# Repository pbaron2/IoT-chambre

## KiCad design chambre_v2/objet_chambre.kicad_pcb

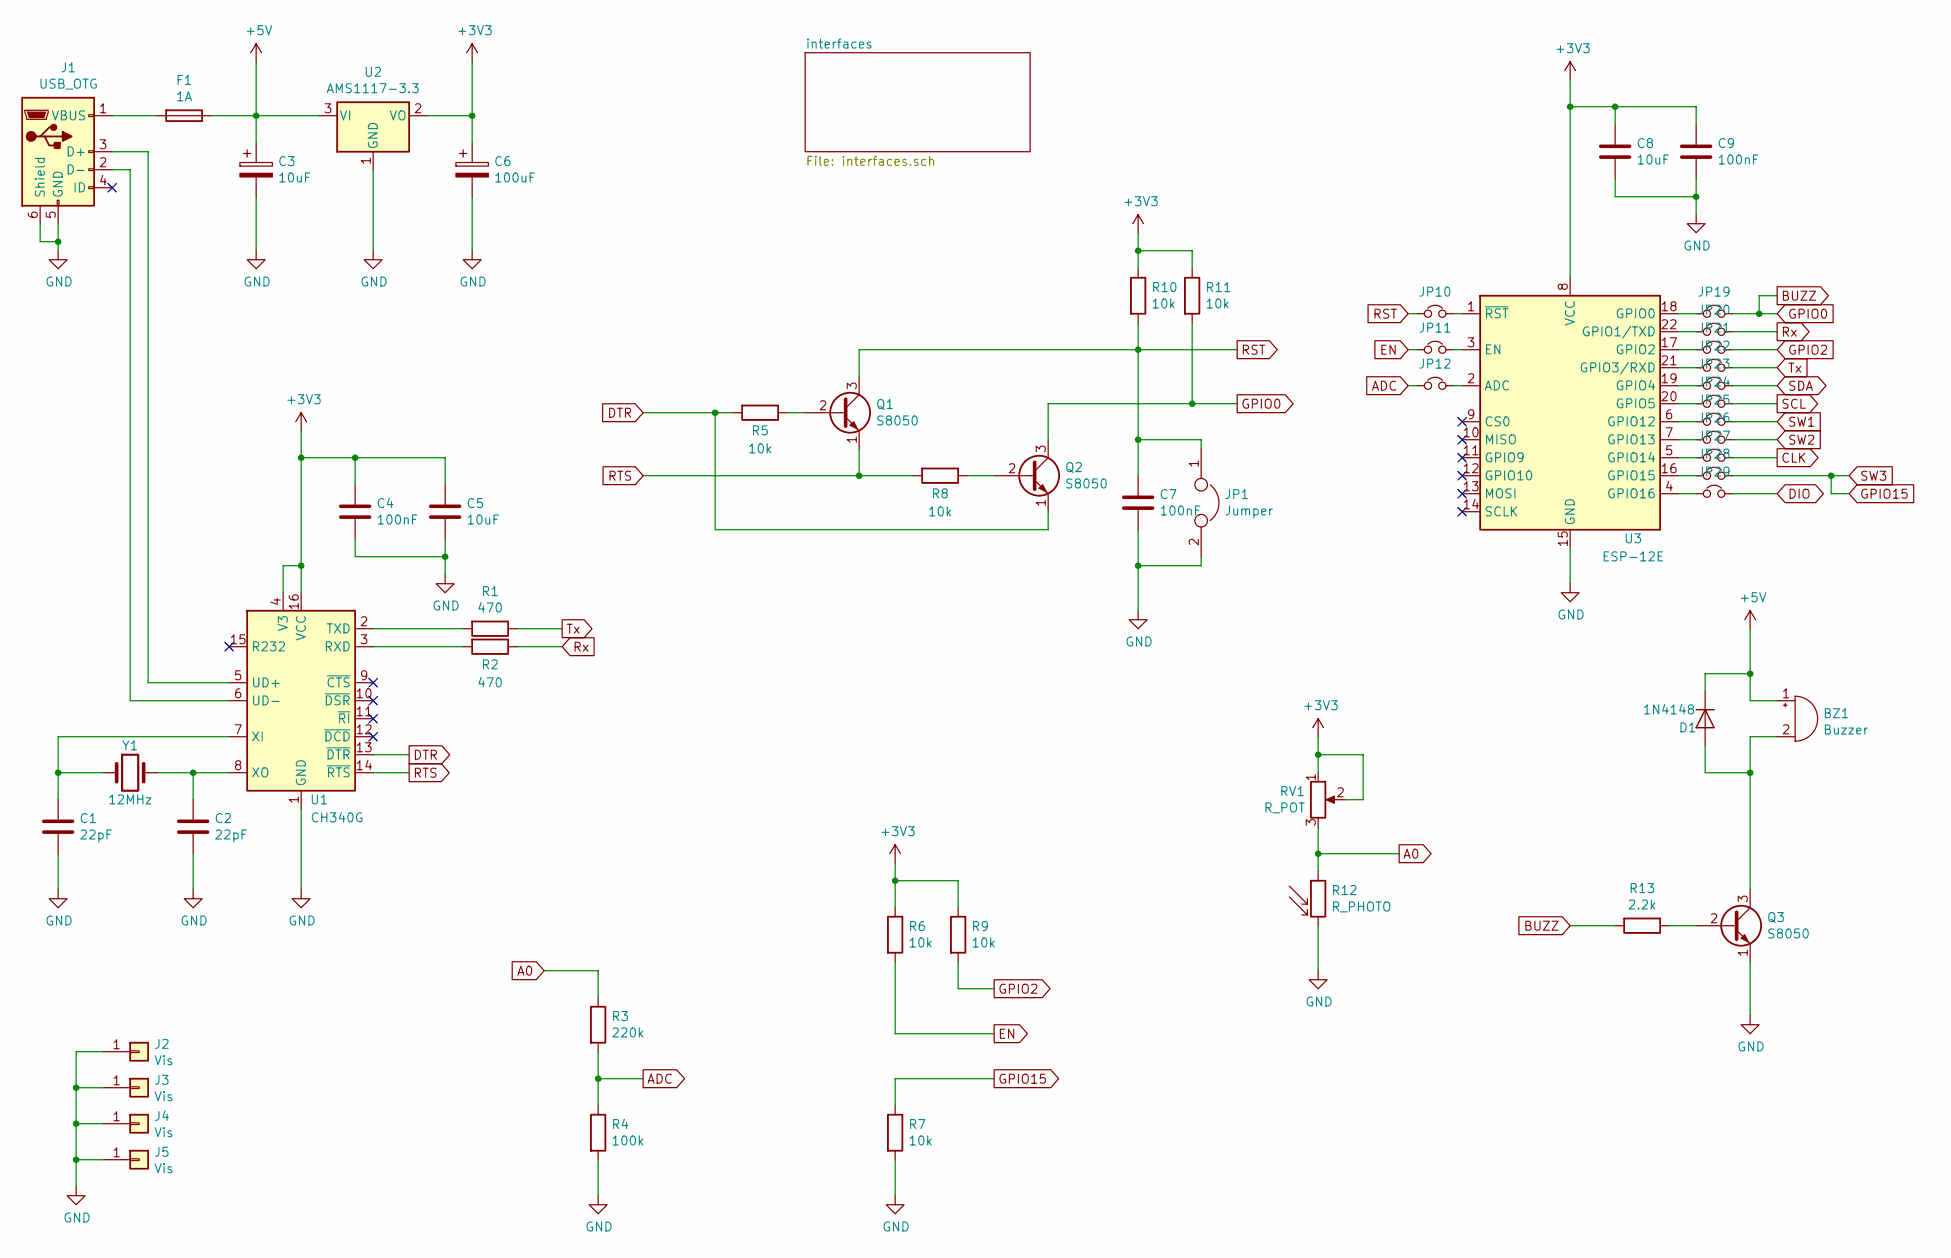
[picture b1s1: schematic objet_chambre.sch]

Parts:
BZ1: Buzzer; CP_Radial_D10.0mm_P5.00mm
C1, C2: 22pF; C_0603_HandSoldering
C3: 10uF; C_1206_HandSoldering
C4, C7, C9: 100nF; C_0603_HandSoldering
C5, C8: 10uF; C_0603_HandSoldering
C6: 100uF; CP_Radial_D6.3mm_P2.50mm
D1: 1N4148; D_DO-35_SOD27_P7.62mm_Horizontal
F1: 1A; Fuse_Littelfuse-LVR100
J1: USB_OTG; USB_Micro-B
J2, J3, J4, J5: Vis; MountingHole_3.2mm_M3_Pad
JP1: Jumper; Pin_Header_Straight_1x02_Pitch2.54mm
JP10, JP11, JP12, JP19, JP20, JP21, JP22, JP23, JP24, JP25, JP26, JP27, JP28, JP29: Jumper_NC; R_0603_HandSoldering
Q1, Q2, Q3: S8050; SOT-23_Handsoldering
R1, R2: 470; R_0805_HandSoldering
R3: 220k; R_0805_HandSoldering
R4: 100k; R_0805_HandSoldering
R5, R6, R7, R8, R9, R10, R11: 10k; R_0805_HandSoldering
R12: R_PHOTO; Resistor_LDR_5.1x4.3_RM3.4
R13: 2.2k; R_0805_HandSoldering
RV1: R_POT; Potentiometer_Trimmer_Bourns_3266Y
U1: CH340G; SOIC-16_3.9x9.9mm_Pitch1.27mm
U2: AMS1117-3.3; SOT-223-3_TabPin2
U3: ESP-12E
Y1: 12MHz; Crystal_HC49-U_Vertical

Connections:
+3V3: C4.1, C5.1, C6.1, C8.1, C9.1, R6.1, R9.1, R10.1, R11.1, RV1.1, RV1.2, U1.4 (V3), U1.16 (VCC), U2.2 (VO), U3.8 (VCC); also elsewhere on the board
+5V: BZ1.1 (-), C3.1, D1.1 (K), F1.1, U2.3 (VI); also elsewhere on the board
A0: R3.1, R12.1, RV1.3
ADC: JP12.1, R3.2, R4.1
BUZZ: JP19.2, Q2.3 (C), R11.2, R13.2
CLK: JP27.2; also elsewhere on the board
DIO: JP29.2; also elsewhere on the board
DTR: Q2.1 (E), R5.2, U1.13 (~DTR)
EN: JP11.1, R6.2
GND: C1.2, C2.2, C3.2, C4.2, C5.2, C6.2, C7.2, C8.2, C9.2, J1.5 (GND), J1.6 (Shield), J2.1, J3.1, J4.1, J5.1, JP1.2, Q3.1 (E), R4.2, R7.2, R12.2, U1.1 (GND), U2.1 (GND), U3.15 (GND); also elsewhere on the board
GPIO2: JP21.2, R9.2
GPIO15: JP28.2, R7.1; also elsewhere on the board
unnamed: BZ1.2 (+), D1.2 (A), Q3.3 (C)
unnamed: C1.1, U1.7 (XI), Y1.1
unnamed: C2.1, U1.8 (XO), Y1.2
unnamed: F1.2, J1.1 (VBUS)
unnamed: J1.2 (D-), U1.6 (UD-)
unnamed: J1.3 (D+), U1.5 (UD+)
unnamed: JP10.2, U3.1 (~RST)
unnamed: JP11.2, U3.3 (EN)
unnamed: JP12.2, U3.2 (ADC)
unnamed: JP19.1, U3.18 (GPIO0)
unnamed: JP20.1, U3.22 (GPIO1/TXD)
unnamed: JP21.1, U3.17 (GPIO2)
unnamed: JP22.1, U3.21 (GPIO3/RXD)
unnamed: JP23.1, U3.19 (GPIO4)
unnamed: JP24.1, U3.20 (GPIO5)
unnamed: JP25.1, U3.6 (GPIO12)
unnamed: JP26.1, U3.7 (GPIO13)
unnamed: JP27.1, U3.5 (GPIO14)
unnamed: JP28.1, U3.16 (GPIO15)
unnamed: JP29.1, U3.4 (GPIO16)
unnamed: Q1.2 (B), R5.1
unnamed: Q2.2 (B), R8.1
unnamed: Q3.2 (B), R13.1
unnamed: R1.2, U1.2 (TXD)
unnamed: R2.2, U1.3 (RXD)
RST: C7.1, JP1.1, JP10.1, Q1.3 (C), R10.2
RTS: Q1.1 (E), R8.2, U1.14 (~RTS)
Rx: JP20.2, R2.1
SCL: JP24.2; also elsewhere on the board
SDA: JP23.2; also elsewhere on the board
SW1: JP25.2; also elsewhere on the board
SW2: JP26.2; also elsewhere on the board
Tx: JP22.2, R1.1

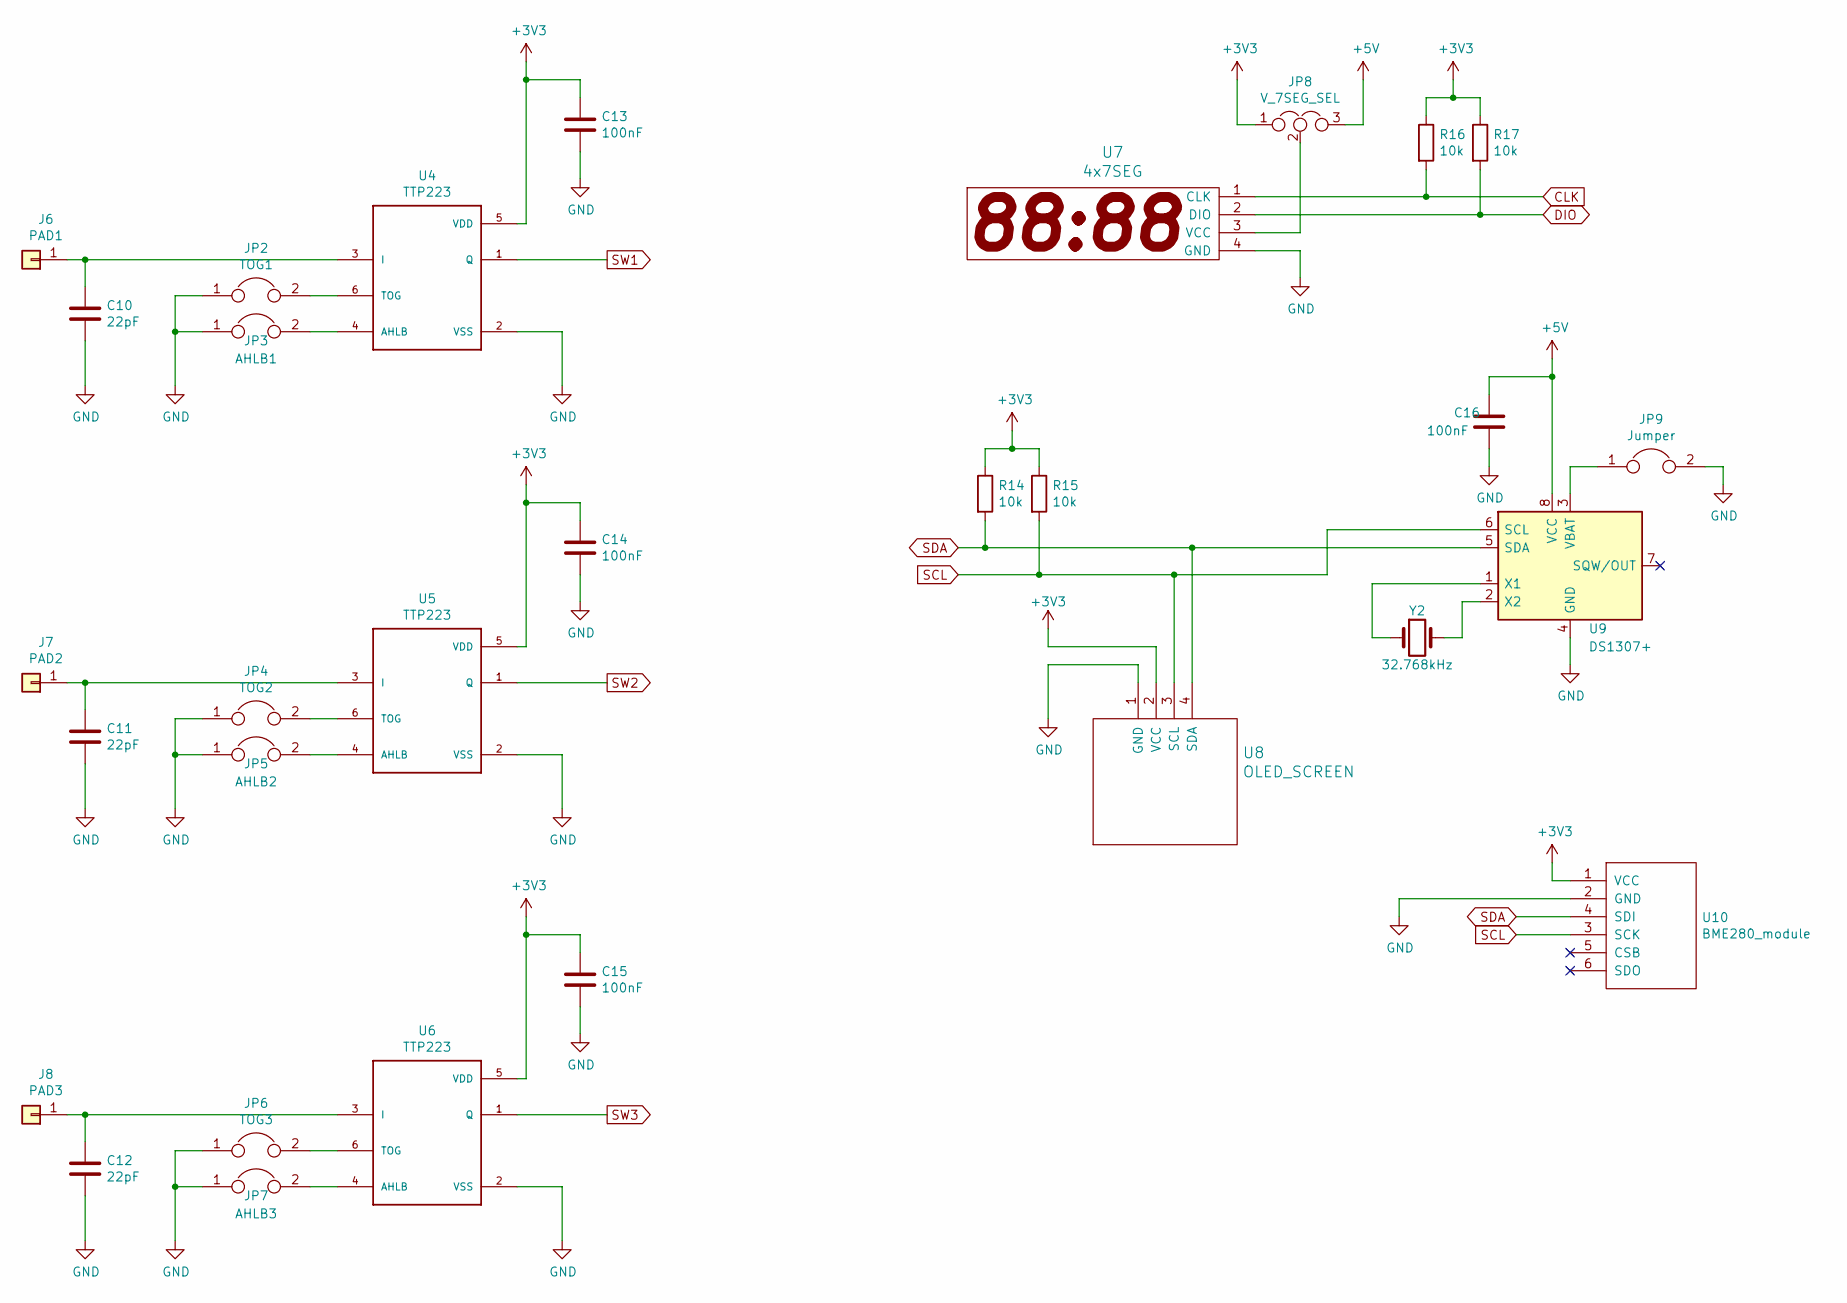
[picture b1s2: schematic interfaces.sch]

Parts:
C10, C11, C12: 22pF; C_0603_HandSoldering
C13, C14, C15, C16: 100nF; C_0603_HandSoldering
J6: PAD1; 1Pin
J7: PAD2; 1Pin
J8: PAD3; 1Pin
JP2: TOG1; R_0603_HandSoldering
JP3: AHLB1; R_0603_HandSoldering
JP4: TOG2; R_0603_HandSoldering
JP5: AHLB2; R_0603_HandSoldering
JP6: TOG3; R_0603_HandSoldering
JP7: AHLB3; R_0603_HandSoldering
JP8: V_7SEG_SEL; Pin_Header_Straight_1x03_Pitch2.54mm
JP9: Jumper; R_0603_HandSoldering
R14, R15, R16, R17: 10k; R_0805_HandSoldering
U4, U5, U6: TTP223; SOT-23-6_Handsoldering
U7: 4x7SEG; Pin_Header_Straight_1x04_Pitch2.54mm
U8: OLED_SCREEN; Pin_Header_Straight_1x04_Pitch2.54mm
U9: DS1307+; SO-8_5.3x6.2mm_Pitch1.27mm
U10: BME280_module; Pin_Header_Straight_1x06_Pitch2.54mm
Y2: 32.768kHz; Crystal_C26-LF_d2.1mm_l6.5mm_Vertical

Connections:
+3V3: C13.1, C14.1, C15.1, JP8.1, R14.1, R15.1, R16.1, R17.1, U4.5 (VDD), U5.5 (VDD), U6.5 (VDD), U8.2 (VCC), U10.1 (VCC); also elsewhere on the board
+5V: C16.1, JP8.3, U9.8 (VCC); also elsewhere on the board
CLK: R16.2, U7.1 (CLK); also elsewhere on the board
DIO: R17.2, U7.2 (DIO); also elsewhere on the board
GND: C10.2, C11.2, C12.2, C13.2, C14.2, C15.2, C16.2, JP2.1, JP3.1, JP4.1, JP5.1, JP6.1, JP7.1, JP9.2, U4.2 (VSS), U5.2 (VSS), U6.2 (VSS), U7.4 (GND), U8.1 (GND), U9.4 (GND), U10.2 (GND); also elsewhere on the board
GPIO15: U6.1 (Q); also elsewhere on the board
unnamed: C10.1, J6.1, U4.3 (I)
unnamed: C11.1, J7.1, U5.3 (I)
unnamed: C12.1, J8.1, U6.3 (I)
unnamed: JP2.2, U4.6 (TOG)
unnamed: JP3.2, U4.4 (AHLB)
unnamed: JP4.2, U5.6 (TOG)
unnamed: JP5.2, U5.4 (AHLB)
unnamed: JP6.2, U6.6 (TOG)
unnamed: JP7.2, U6.4 (AHLB)
unnamed: JP8.2, U7.3 (VCC)
unnamed: JP9.1, U9.3 (VBAT)
unnamed: U9.1 (X1), Y2.1
unnamed: U9.2 (X2), Y2.2
SCL: R15.2, U8.3 (SCL), U9.6 (SCL), U10.3 (SCK); also elsewhere on the board
SDA: R14.2, U8.4 (SDA), U9.5 (SDA), U10.4 (SDI); also elsewhere on the board
SW1: U4.1 (Q); also elsewhere on the board
SW2: U5.1 (Q); also elsewhere on the board

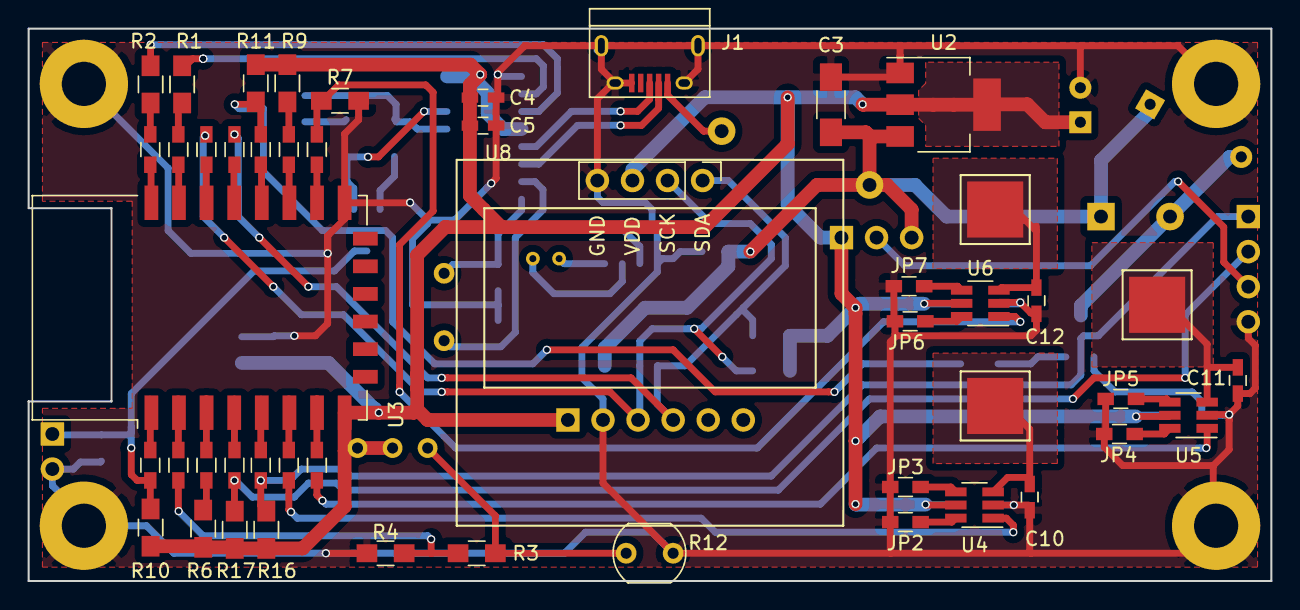
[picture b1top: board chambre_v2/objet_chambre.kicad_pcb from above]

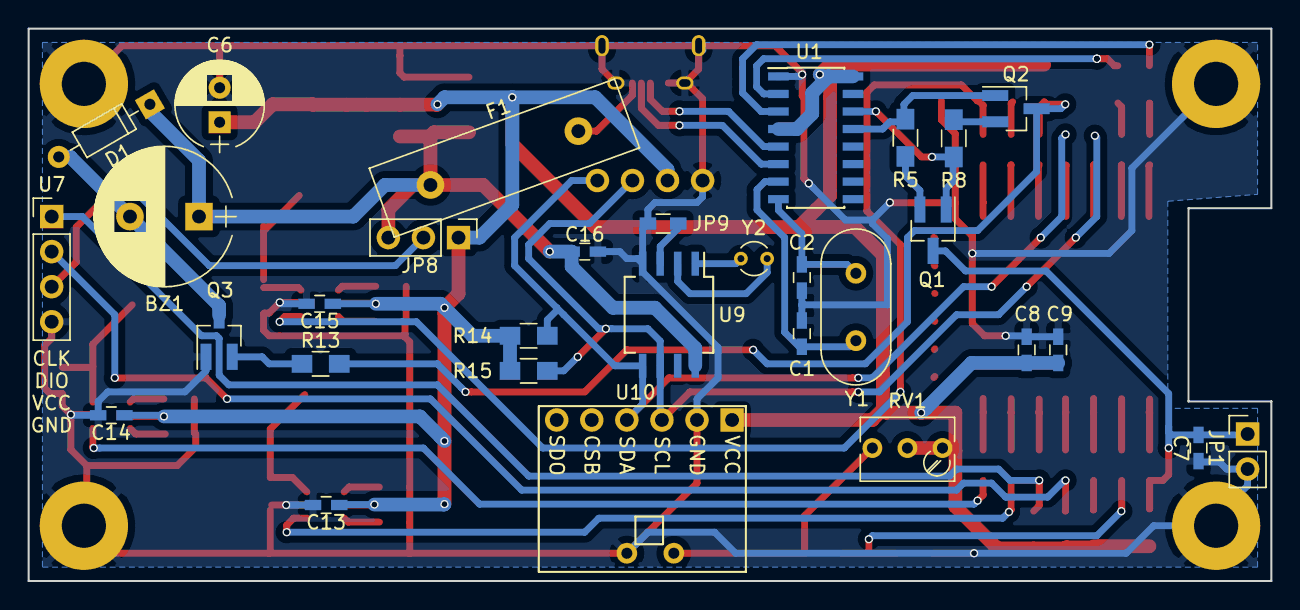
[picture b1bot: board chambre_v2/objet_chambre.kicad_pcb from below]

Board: 2 copper layers, 90.0 x 40.0 mm, 83 parts (31 on the bottom side), 58 nets.

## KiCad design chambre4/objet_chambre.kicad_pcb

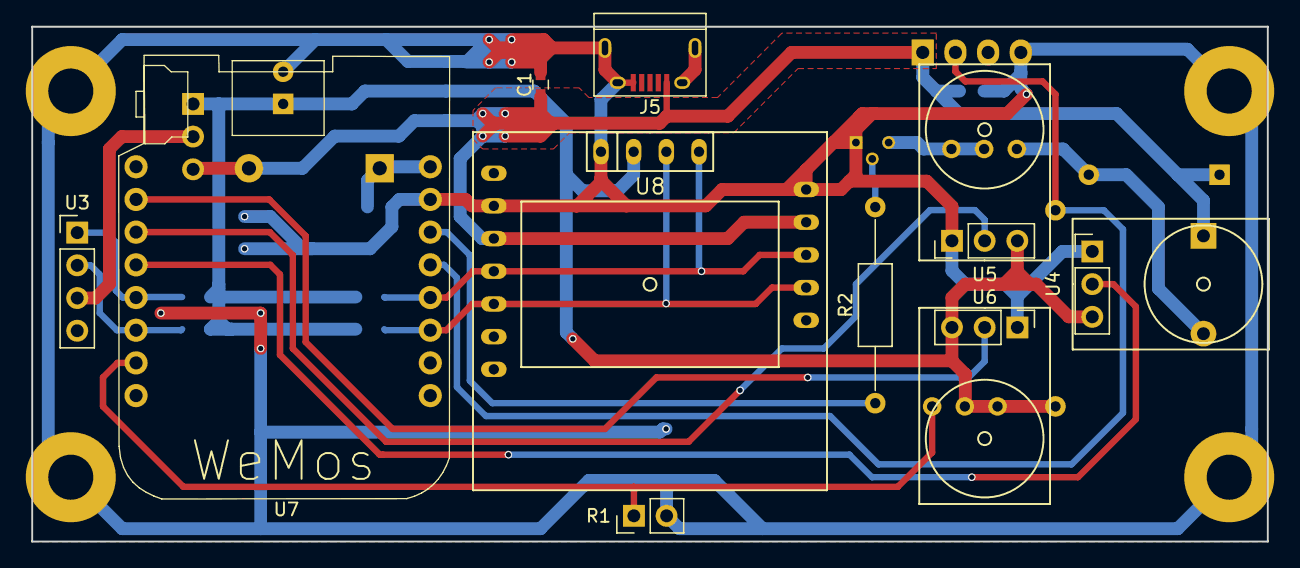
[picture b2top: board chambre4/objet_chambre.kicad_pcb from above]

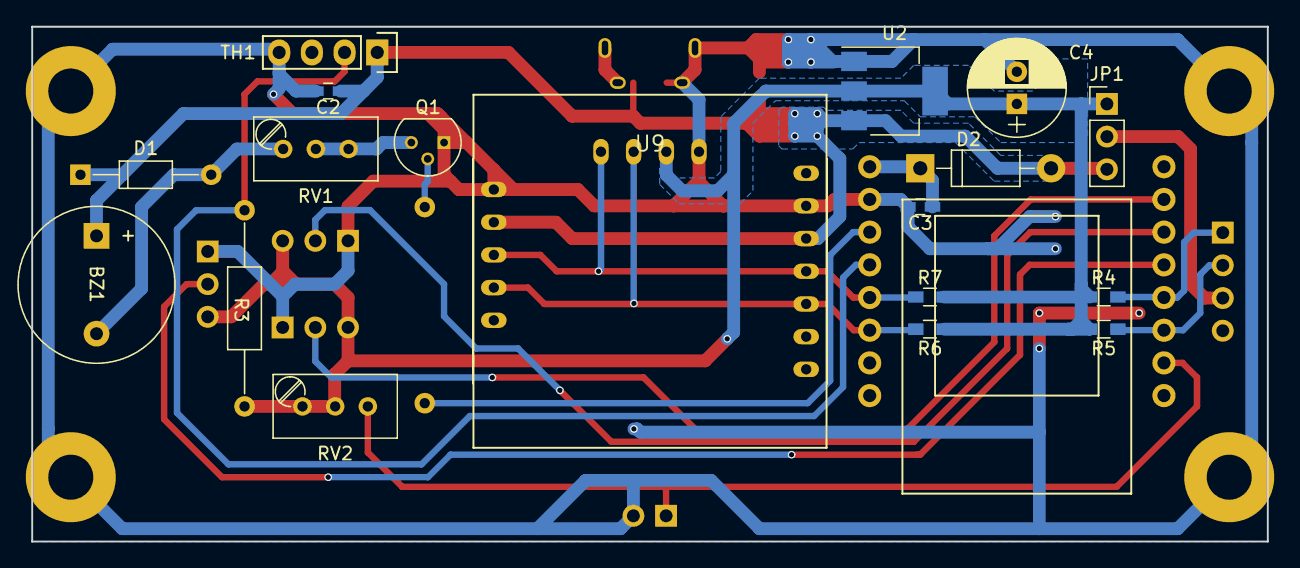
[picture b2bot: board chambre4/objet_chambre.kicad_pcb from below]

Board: 2 copper layers, 96.0 x 40.0 mm, 32 parts (18 on the bottom side), 18 nets.

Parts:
BZ1: Buzzer; Buzzer_12x9.5RM7.6
C1: 10uF; C_0603_HandSoldering
C2, C3: 10nF; C_0603_HandSoldering
C4: 100uF; CP_Radial_D7.5mm_P2.50mm
D1: 1N4148; D_DO-35_SOD27_P10.16mm_Horizontal
D2: 1N4007; D_DO-41_SOD81_P10.16mm_Horizontal
J1, J2, J3, J4: Conn_01x01; MountingHole_3.5mm_Pad
J5: USB_OTG; USB_Micro-B
JP1: Jumper; Pin_Header_Straight_1x03_Pitch2.54mm
Q1: PN2222A; TO-92_Molded_Narrow
R1: R_PHOTO; Pin_Header_Straight_1x02_Pitch2.54mm
R2: 2.2k; R_Axial_DIN0207_L6.3mm_D2.5mm_P15.24mm_Horizontal
R3: 1k; R_Axial_DIN0207_L6.3mm_D2.5mm_P15.24mm_Horizontal
R4, R5, R6, R7: 10k; R_0603_HandSoldering
RV1: 500; Potentiometer_Trimmer_Bourns_3296W
RV2: 50k; Potentiometer_Trimmer_Bourns_3296W
TH1: DHT22; DHT22_Temperature_Humidity
U2: AZ1117-3.3; SOT-223-3_TabPin2
U3: 4x7SEG; Pin_Header_Straight_1x04_Pitch2.54mm
U4, U5, U6: TouchPad; TouchPad_TTP223
U7: WeMos_mini; D1_mini_board
U8: OLED_SCREEN; OLED_SCREEN_SSD1306
U9: DS1307

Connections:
+3V3: C4.1, JP1.1, R3.1, R4.1, R5.1, R6.1, R7.1, RV2.1, RV2.2, U2.2, U4.3, U5.3, U6.3, U8.2
+5V: BZ1.1, C1.1, C2.1, D1.1, D2.2, J5.1, JP1.3, TH1.1, U2.3, U9.3, U9.11
BUZZ: R2.1, U7.3
CLK: R4.2, U3.1, U7.12
DATA_DHT: R3.2, TH1.2, U7.4
DIO: R5.2, U3.2, U7.11
GNDPWR: C1.2, C2.2, C3.2, C4.2, J1.1, J2.1, J3.1, J4.1, J5.5, J5.6, Q1.1, R1.2, TH1.4, U2.1, U3.4, U4.1, U5.1, U6.1, U7.2, U8.1, U9.2, U9.12
unnamed: BZ1.2, D1.2, RV1.1
unnamed: C3.1, D2.1, U7.1
unnamed: JP1.2, U3.3
unnamed: Q1.2, R2.2
unnamed: Q1.3, RV1.2, RV1.3
PHOTORES: R1.1, RV2.3, U7.10
SCL: R6.2, U7.6, U8.3, U9.5, U9.9
SDA: R7.2, U7.5, U8.4, U9.4, U9.10
SW1: U4.2, U7.13
SW2: U5.2, U7.14
SW3: U6.2, U7.15

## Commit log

2020-01-18 change mqtt settiings to new rpi mqtt config, and light improvements
2020-01-18 eeprom and mqtt connect fixes
2020-04-12 faster luminosity update send luminosity by mqtt no longer wifi access point arduinojson updated to v6.14.1
2020-04-13 add dimming of oled when lunimosity is 0 add config png
2020-04-13 add pcb v2
2020-05-24 change sensor from DHT22 to BME280
2020-05-24 add wifimanager
